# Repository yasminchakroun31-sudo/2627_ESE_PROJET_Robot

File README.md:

# 2627_ESE_PROJET_PAC-Man🤖🗑️
PAC-Man 

### Équipe
- **Yesmine Chakroun** (yasminechakroun31-sudo)
- **Wejdene Hazami**
- **Roua Jaouadi**

### Objectif
Concevoir un robot mobile qui repère, attrape, différencie et dépose des canettes en fonction de leur couleur.

### Timeline
- **Challenge:** 15 janvier 2027
- **Fin semestre:** 16 janvier 2027

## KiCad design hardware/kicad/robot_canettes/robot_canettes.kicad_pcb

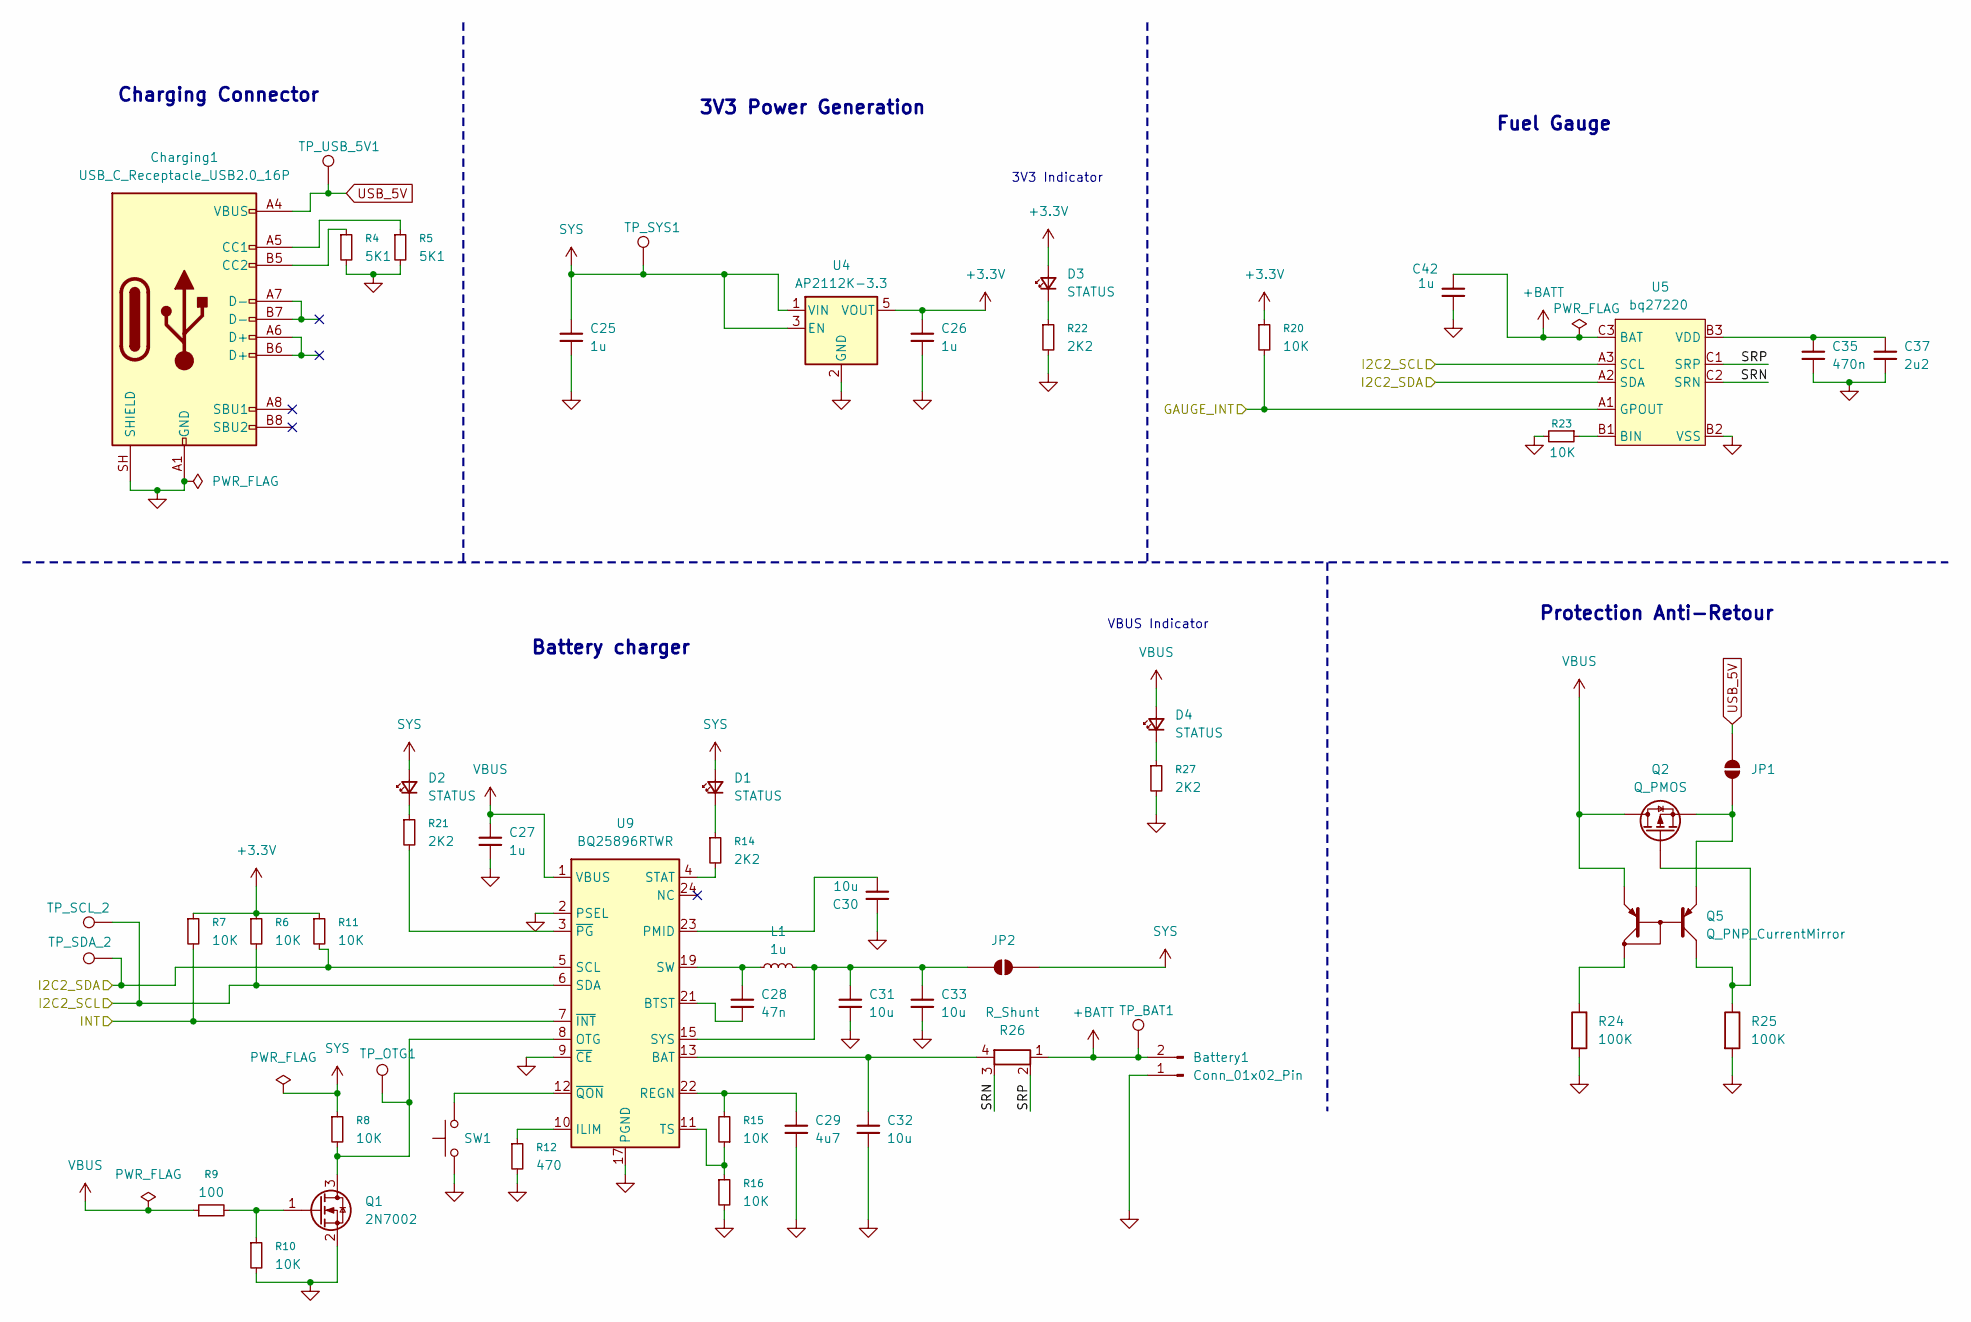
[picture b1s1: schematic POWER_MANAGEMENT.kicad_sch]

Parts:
Battery1: Conn_01x02_Pin; JST_PH_B2B-PH-K_1x02_P2.00mm_Vertical; JLCPCB Part # C131337
C25, C26, C27, C42: 1u; C_0402_1005Metric; JLCPCB Part # C52923
C28: 47n; C_0402_1005Metric; JLCPCB Part # C5254486
C29: 4u7; C_0402_1005Metric; JLCPCB Part # C368809
C30, C31, C32, C33: 10u; C_0603_1608Metric; JLCPCB Part # C19702
C35: 470n; C_0402_1005Metric; JLCPCB Part # C2443202
C37: 2u2; C_0402_1005Metric; JLCPCB Part # C12530
Charging1: USB_C_Receptacle_USB2.0_16P; USB_C_Receptacle_GCT_USB4105-xx-A_16P_TopMnt_Horizontal; JLCPCB Part # C2765186
D1: STATUS; LED_0603_1608Metric; JLCPCB Part # C2287
D2, D3, D4: STATUS; LED_0603_1608Metric; JLCPCB Part # C12624
JP1, JP2: SolderJumper-2_P1.3mm_Open_Pad1.0x1.5mm
L1: 1u; L_APV_ANR4010; JLCPCB Part # C354578
Q1: 2N7002; SOT-23; JLCPCB Part # C8545
Q2: Q_PMOS; SOT-23; JLCPCB Part # C177033
Q5: Q_PNP_CurrentMirror; SOT-363_SC-70-6; JLCPCB Part # C42387345
R4, R5: 5K1; R_0402_1005Metric; JLCPCB Part # C25905
R6, R7, R8, R10, R11, R15, R16, R20, R23: 10K; R_0402_1005Metric; JLCPCB Part # C25744
R9: 100; R_0402_1005Metric; JLCPCB Part # C25076
R12: 470; R_0402_1005Metric; JLCPCB Part # C25117
R14, R21, R22, R27: 2K2; R_0402_1005Metric; JLCPCB Part # C25879
R24, R25: 100K; R_0603_1608Metric; JLCPCB Part # C25803
R26: R_Shunt; R_Shunt_Ohmite_LVK12; JLCPCB Part # C2903499
SW1: SW_SPST_Omron_B3FS-101xP; JLCPCB Part # C271753
TP_BAT1: TestPoint_Pad_D1.5mm
TP_OTG1: TestPoint_Pad_D1.5mm
TP_SCL_2: TestPoint_Pad_D1.5mm
TP_SDA_2: TestPoint_Pad_D1.5mm
TP_SYS1: TestPoint_Pad_D1.5mm
TP_USB_5V1: TestPoint_Pad_D1.5mm
U4: AP2112K-3.3; SOT-23-5; JLCPCB Part # C51118
U5: bq27220; BGA-9_3x3_1.62x1.58mm_Pitch0.5mm; JLCPCB Part # C528617
U9: BQ25896RTWR; Texas_RTW_WQFN-24-1EP_4x4mm_P0.5mm_EP2.7x2.7mm_ThermalVias; JLCPCB Part # C181475

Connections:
+3.3V: C26.1, D3.2 (A), R6.1, R7.1, R11.1, R20.1, U4.5 (VOUT); also elsewhere on the board
+BATT: Battery1.2, C42.2, R26.1, TP_BAT1.1 (1_1), U5.C3 (BAT)
/MCU/GAUGE_INT: R20.2, U5.A1 (GPOUT); also elsewhere on the board
/MCU/I2C2_SCL: R6.2, TP_SCL_2.1 (1_1), U5.A3 (SCL), U9.6 (SDA); also elsewhere on the board
/MCU/I2C2_SDA: R11.2, TP_SDA_2.1 (1_1), U5.A2 (SDA), U9.5 (SCL); also elsewhere on the board
/MCU/INT: R7.2, U9.7 (~INT); also elsewhere on the board
/POWER_MANAGEMENT/SRN: R26.3, U5.C2 (SRN)
/POWER_MANAGEMENT/SRP: R26.2, U5.C1 (SRP)
unnamed: C28.1, L1.1, U9.19 (SW), U9.20 (SW)
unnamed: C32.1, R26.4, U9.13 (BAT), U9.14 (BAT)
unnamed: D1.1 (K), R14.1
unnamed: D2.1 (K), R21.1
unnamed: D3.1 (K), R22.1
unnamed: D4.1 (K), R27.1
unnamed: Charging1.A5 (CC1), R5.1
unnamed: Charging1.B5 (CC2), R4.1
unnamed: JP1.1 (A), Q2.2 (S), Q5.1 (E1)
unnamed: C31.1, C33.1, JP2.2 (B), L1.2, U9.15 (SYS), U9.16 (SYS)
unnamed: Q1.3 (D), R8.2, TP_OTG1.1 (1_1), U9.8 (OTG)
unnamed: Q1.1 (G), R9.2, R10.1
unnamed: Q2.1 (G), Q5.6 (C1), R25.1
unnamed: Q5.3 (C2), R24.1
unnamed: R23.1, U5.B1 (BIN)
unnamed: C35.1, C37.1, U5.B3 (VDD)
unnamed: C28.2, U9.21 (BTST)
unnamed: R12.1, U9.10 (ILIM)
unnamed: C30.2, U9.23 (PMID)
unnamed: C29.1, R15.2, U9.22 (REGN)
unnamed: R14.2, U9.4 (STAT)
unnamed: R15.1, R16.1, U9.11 (TS)
unnamed: R21.2, U9.3 (~PG)
unnamed: SW1.2, U9.12 (~QON)
SYS: C25.1, D1.2 (A), D2.2 (A), JP2.1 (A), R8.1, TP_SYS1.1 (1_1), U4.1 (VIN), U4.3 (EN)
USB_5V: Charging1.A4 (VBUS), Charging1.A9 (VBUS), Charging1.B4 (VBUS), Charging1.B9 (VBUS), JP1.2 (B), TP_USB_5V1.1 (1_1)
VBUS: C27.1, D4.2 (A), Q2.3 (D), Q5.4 (E2), R9.1, U9.1 (VBUS); also elsewhere on the board

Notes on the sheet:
Battery charger
Charging Connector
3V3 Indicator
Fuel Gauge
3V3 Power Generation
Protection Anti-Retour
VBUS Indicator

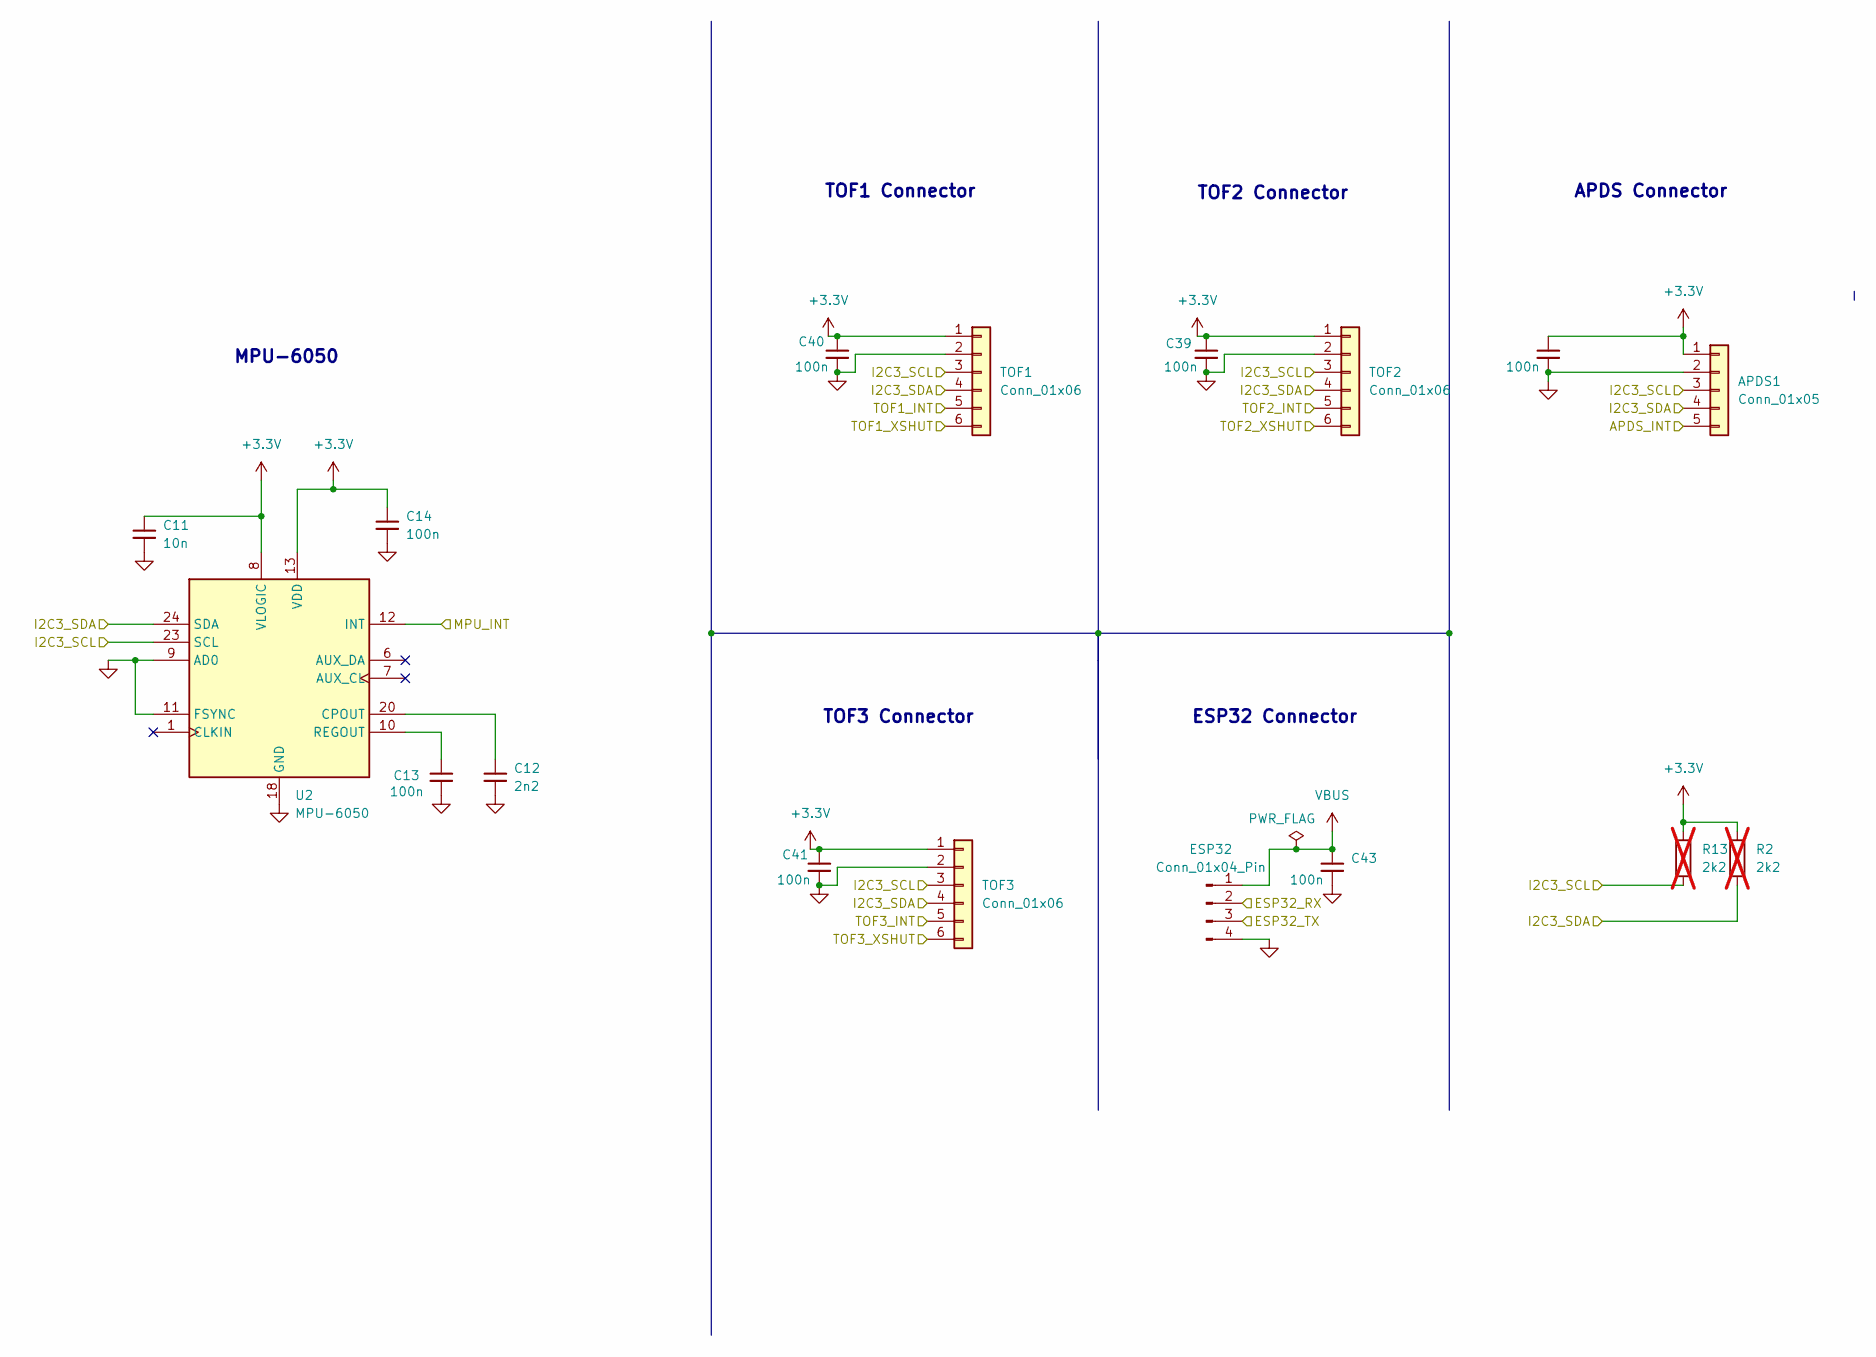
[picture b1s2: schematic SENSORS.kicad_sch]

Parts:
APDS1: Conn_01x05; JST_PH_B5B-PH-K_1x05_P2.00mm_Vertical; JLCPCB Part # C157993
C11: 10n; C_0402_1005Metric; JLCPCB Part # C15195
C12: 2n2; C_0402_1005Metric; JLCPCB Part # C1531
C13, C14, C38, C39, C40, C41, C43: 100n; C_0402_1005Metric; JLCPCB Part # C1525
ESP32: Conn_01x04_Pin; JST_PH_B4B-PH-K_1x04_P2.00mm_Vertical; JLCPCB Part # C131334
R2, R13: 2k2; R_0402_1005Metric; JLCPCB Part # C25879; not fitted
TOF1, TOF2, TOF3: Conn_01x06; JST_PH_B6B-PH-K_1x06_P2.00mm_Vertical; JLCPCB Part # C131342
U2: MPU-6050; InvenSense_QFN-24_4x4mm_P0.5mm; JLCPCB Part # C24112

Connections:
+3.3V: APDS1.1, C11.1, C14.1, C38.1, C39.1, C40.1, C41.1, R2.1, R13.1, TOF1.1, TOF2.1, TOF3.1, U2.8 (VLOGIC), U2.13 (VDD); also elsewhere on the board
/MCU/APDS_INT: APDS1.5; also elsewhere on the board
/MCU/ESP32_RX: ESP32.3; also elsewhere on the board
/MCU/ESP32_TX: ESP32.2; also elsewhere on the board
/MCU/I2C3_SCL: APDS1.3, R13.2, TOF1.3, TOF2.3, TOF3.3, U2.23 (SCL); also elsewhere on the board
/MCU/I2C3_SDA: APDS1.4, R2.2, TOF1.4, TOF2.4, TOF3.4, U2.24 (SDA); also elsewhere on the board
/MCU/MPU_INT: U2.12 (INT); also elsewhere on the board
/MCU/TOF1_INT: TOF1.5; also elsewhere on the board
/MCU/TOF1_XSHUT: TOF1.6; also elsewhere on the board
/MCU/TOF2_INT: TOF2.5; also elsewhere on the board
/MCU/TOF2_XSHUT: TOF2.6; also elsewhere on the board
/MCU/TOF3_INT: TOF3.5; also elsewhere on the board
/MCU/TOF3_XSHUT: TOF3.6; also elsewhere on the board
unnamed: C12.1, U2.20 (CPOUT)
unnamed: C13.1, U2.10 (REGOUT)
VBUS: C43.1, ESP32.1; also elsewhere on the board

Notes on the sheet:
TOF1 Connector
APDS Connector
ESP32 Connector
TOF2 Connector
MPU-6050
TOF3 Connector

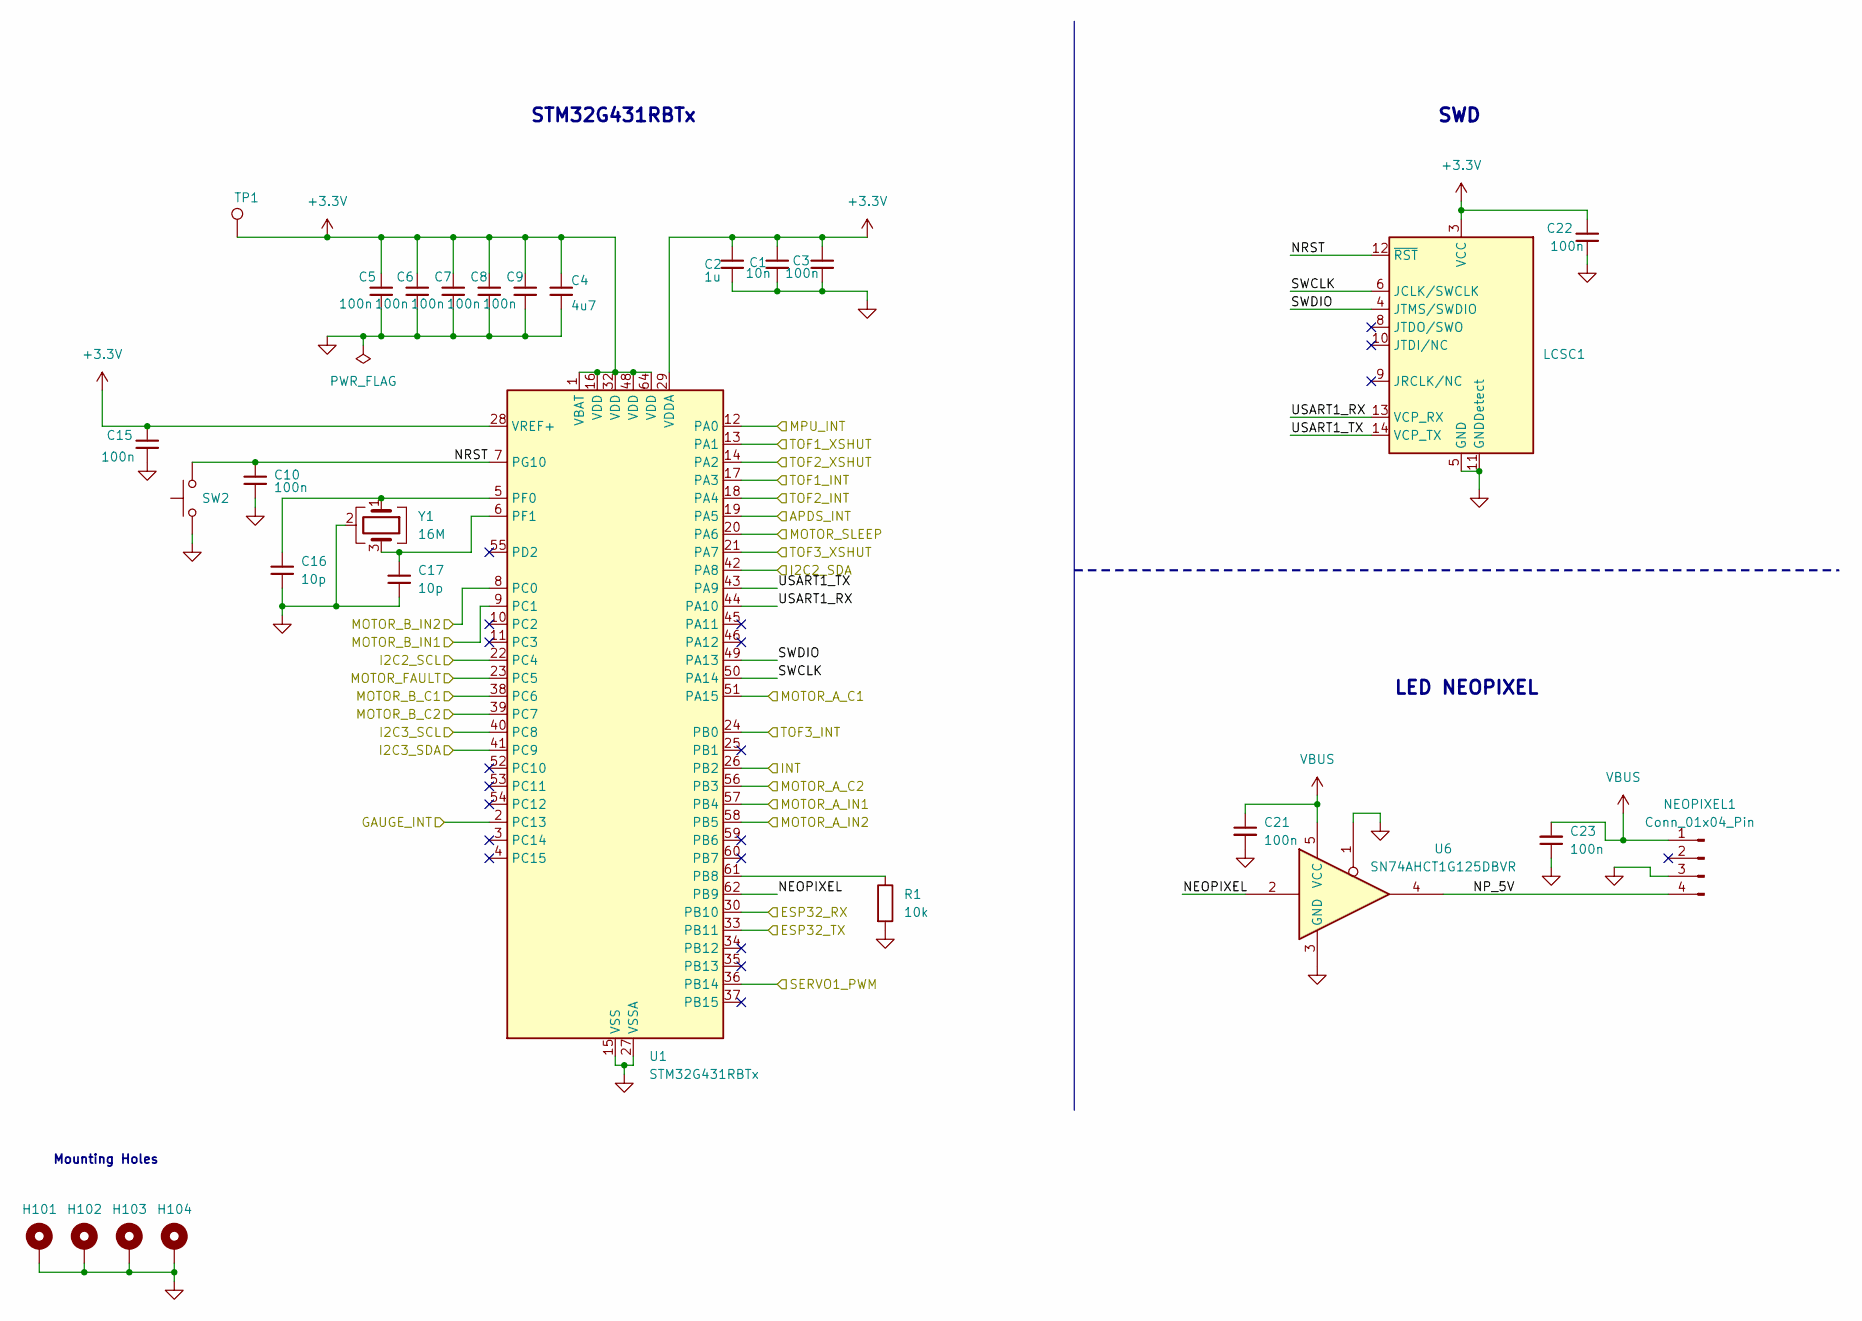
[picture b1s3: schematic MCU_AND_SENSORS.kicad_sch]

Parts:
C1: 10n; C_0402_1005Metric; JLCPCB Part # C15195
C2: 1u; C_0603_1608Metric; JLCPCB Part # C141772
C3, C5, C6, C7, C8, C9, C10, C15, C21, C22, C23: 100n; C_0402_1005Metric; JLCPCB Part # C1525
C4: 4u7; C_0603_1608Metric; JLCPCB Part # C19666
C16, C17: 10p; C_0603_1608Metric; JLCPCB Part # C281766
H101, H102, H103, H104: MountingHole_Pad; MountingHole_3.2mm_M3_Pad_Via
LCSC1: PinHeader_2x07_P1.27mm_Vertical_SMD; JLCPCB Part # C3975190
NEOPIXEL1: Conn_01x04_Pin; JST_PH_B4B-PH-K_1x04_P2.00mm_Vertical; JLCPCB Part # C131334
R1: 10k; R_0402_1005Metric; JLCPCB Part # C25744
SW2: SW_SPST_Omron_B3FS-101xP; JLCPCB Part # C271753
TP1: TestPoint; TestPoint_Pad_D1.5mm
U1: STM32G431RBTx; LQFP-64_10x10mm_P0.5mm; JLCPCB Part # C431633
U6: SN74AHCT1G125DBVR; SOT-23-5; JLCPCB Part # C7484
Y1: 16M; Crystal_SMD_EuroQuartz_MT-4Pin_3.2x2.5mm; JLCPCB Part # C13738

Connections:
+3.3V: C1.1, C2.1, C3.1, C4.1, C5.1, C6.1, C7.1, C8.1, C9.1, C15.1, C22.1, LCSC1.3 (VCC), TP1.1 (1_1), U1.1 (VBAT), U1.16 (VDD), U1.28 (VREF+), U1.29 (VDDA), U1.32 (VDD), U1.48 (VDD), U1.64 (VDD); also elsewhere on the board
/MCU/APDS_INT: U1.19 (PA5); also elsewhere on the board
/MCU/ESP32_RX: U1.30 (PB10); also elsewhere on the board
/MCU/ESP32_TX: U1.33 (PB11); also elsewhere on the board
/MCU/GAUGE_INT: U1.2 (PC13); also elsewhere on the board
/MCU/I2C2_SCL: U1.22 (PC4); also elsewhere on the board
/MCU/I2C2_SDA: U1.42 (PA8); also elsewhere on the board
/MCU/I2C3_SCL: U1.40 (PC8); also elsewhere on the board
/MCU/I2C3_SDA: U1.41 (PC9); also elsewhere on the board
/MCU/INT: U1.26 (PB2); also elsewhere on the board
/MCU/MOTOR_A_C1: U1.51 (PA15); also elsewhere on the board
/MCU/MOTOR_A_C2: U1.56 (PB3); also elsewhere on the board
/MCU/MOTOR_A_IN1: U1.57 (PB4); also elsewhere on the board
/MCU/MOTOR_A_IN2: U1.58 (PB5); also elsewhere on the board
/MCU/MOTOR_B_C1: U1.38 (PC6); also elsewhere on the board
/MCU/MOTOR_B_C2: U1.39 (PC7); also elsewhere on the board
/MCU/MOTOR_B_IN1: U1.9 (PC1); also elsewhere on the board
/MCU/MOTOR_B_IN2: U1.8 (PC0); also elsewhere on the board
/MCU/MOTOR_FAULT: U1.23 (PC5); also elsewhere on the board
/MCU/MOTOR_SLEEP: U1.20 (PA6); also elsewhere on the board
/MCU/MPU_INT: U1.12 (PA0); also elsewhere on the board
/MCU/NEOPIXEL: U1.62 (PB9), U6.2
/MCU/NP_5V: NEOPIXEL1.4, U6.4
/MCU/NRST: C10.1, LCSC1.12 (~RST), SW2.2, U1.7 (PG10)
/MCU/SERVO1_PWM: U1.36 (PB14); also elsewhere on the board
/MCU/SWCLK: LCSC1.6 (JCLK/SWCLK), U1.50 (PA14)
/MCU/SWDIO: LCSC1.4 (JTMS/SWDIO), U1.49 (PA13)
/MCU/TOF1_INT: U1.17 (PA3); also elsewhere on the board
/MCU/TOF1_XSHUT: U1.13 (PA1); also elsewhere on the board
/MCU/TOF2_INT: U1.18 (PA4); also elsewhere on the board
/MCU/TOF2_XSHUT: U1.14 (PA2); also elsewhere on the board
/MCU/TOF3_INT: U1.24 (PB0); also elsewhere on the board
/MCU/TOF3_XSHUT: U1.21 (PA7); also elsewhere on the board
/MCU/USART1_RX: LCSC1.13 (VCP_RX), U1.44 (PA10)
/MCU/USART1_TX: LCSC1.14 (VCP_TX), U1.43 (PA9)
unnamed: R1.1, U1.61 (PB8)
unnamed: C16.1, U1.5 (PF0), Y1.1
unnamed: C17.1, U1.6 (PF1), Y1.3
VBUS: C21.1, C23.2, NEOPIXEL1.1, U6.5 (VCC); also elsewhere on the board

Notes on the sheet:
LED NEOPIXEL
SWD
Mounting Holes
STM32G431RBTx

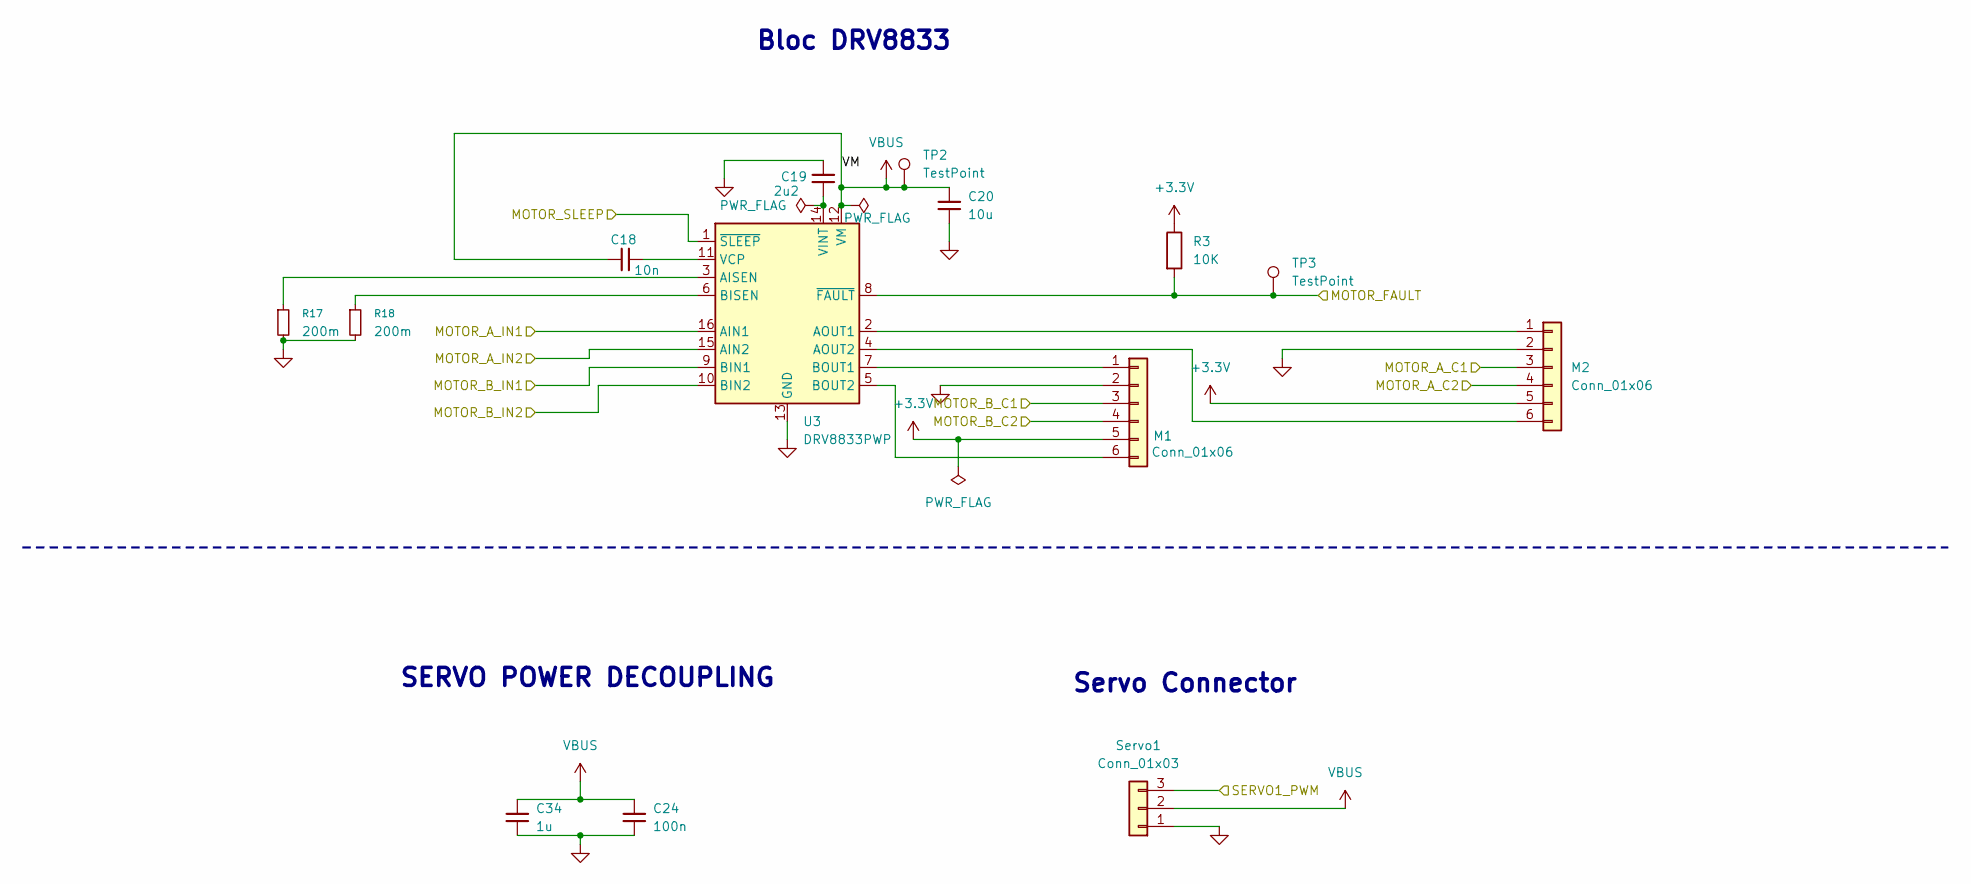
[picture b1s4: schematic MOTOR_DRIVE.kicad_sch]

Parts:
C18: 10n; C_0402_1005Metric; JLCPCB Part # C15195
C19: 2u2; C_0402_1005Metric; JLCPCB Part # C12530
C20: 10u; C_0805_2012Metric; JLCPCB Part # C380332
C24: 100n; C_0402_1005Metric; JLCPCB Part # C1525
C34: 1u; C_0402_1005Metric; JLCPCB Part # C52923
M1, M2: Conn_01x06; JST_PH_B6B-PH-K_1x06_P2.00mm_Vertical; JLCPCB Part # C131342
R3: 10K; R_0402_1005Metric; JLCPCB Part # C25744
R17, R18: 200m; R_1206_3216Metric; JLCPCB Part # C5127778
Servo1: Conn_01x03; JST_PH_B3B-PH-K_1x03_P2.00mm_Vertical; JLCPCB Part # C131339
TP2, TP3: TestPoint; TestPoint_Pad_D1.5mm
U3: DRV8833PWP; HTSSOP-16-1EP_4.4x5mm_P0.65mm_EP3.4x5mm_Mask2.46x2.31mm; JLCPCB Part # C50506

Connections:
+3.3V: M1.5, M2.5, R3.1; also elsewhere on the board
/MCU/MOTOR_A_C1: M2.3; also elsewhere on the board
/MCU/MOTOR_A_C2: M2.4; also elsewhere on the board
/MCU/MOTOR_A_IN1: U3.16 (AIN1); also elsewhere on the board
/MCU/MOTOR_A_IN2: U3.15 (AIN2); also elsewhere on the board
/MCU/MOTOR_B_C1: M1.3; also elsewhere on the board
/MCU/MOTOR_B_C2: M1.4; also elsewhere on the board
/MCU/MOTOR_B_IN1: U3.9 (BIN1); also elsewhere on the board
/MCU/MOTOR_B_IN2: U3.10 (BIN2); also elsewhere on the board
/MCU/MOTOR_FAULT: R3.2, TP3.1 (1_1), U3.8 (~FAULT); also elsewhere on the board
/MCU/MOTOR_SLEEP: U3.1 (~SLEEP); also elsewhere on the board
/MCU/SERVO1_PWM: Servo1.3; also elsewhere on the board
unnamed: M1.1, U3.7 (BOUT1)
unnamed: M1.6, U3.5 (BOUT2)
unnamed: M2.1, U3.2 (AOUT1)
unnamed: M2.6, U3.4 (AOUT2)
unnamed: R17.1, U3.3 (AISEN)
unnamed: R18.1, U3.6 (BISEN)
unnamed: C18.2, U3.11 (VCP)
unnamed: C19.2, U3.14 (VINT)
VBUS: C18.1, C20.1, C24.1, C34.1, Servo1.2, TP2.1 (1_1), U3.12 (VM); also elsewhere on the board

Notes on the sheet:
Servo Connector
SERVO POWER DECOUPLING
Bloc DRV8833

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
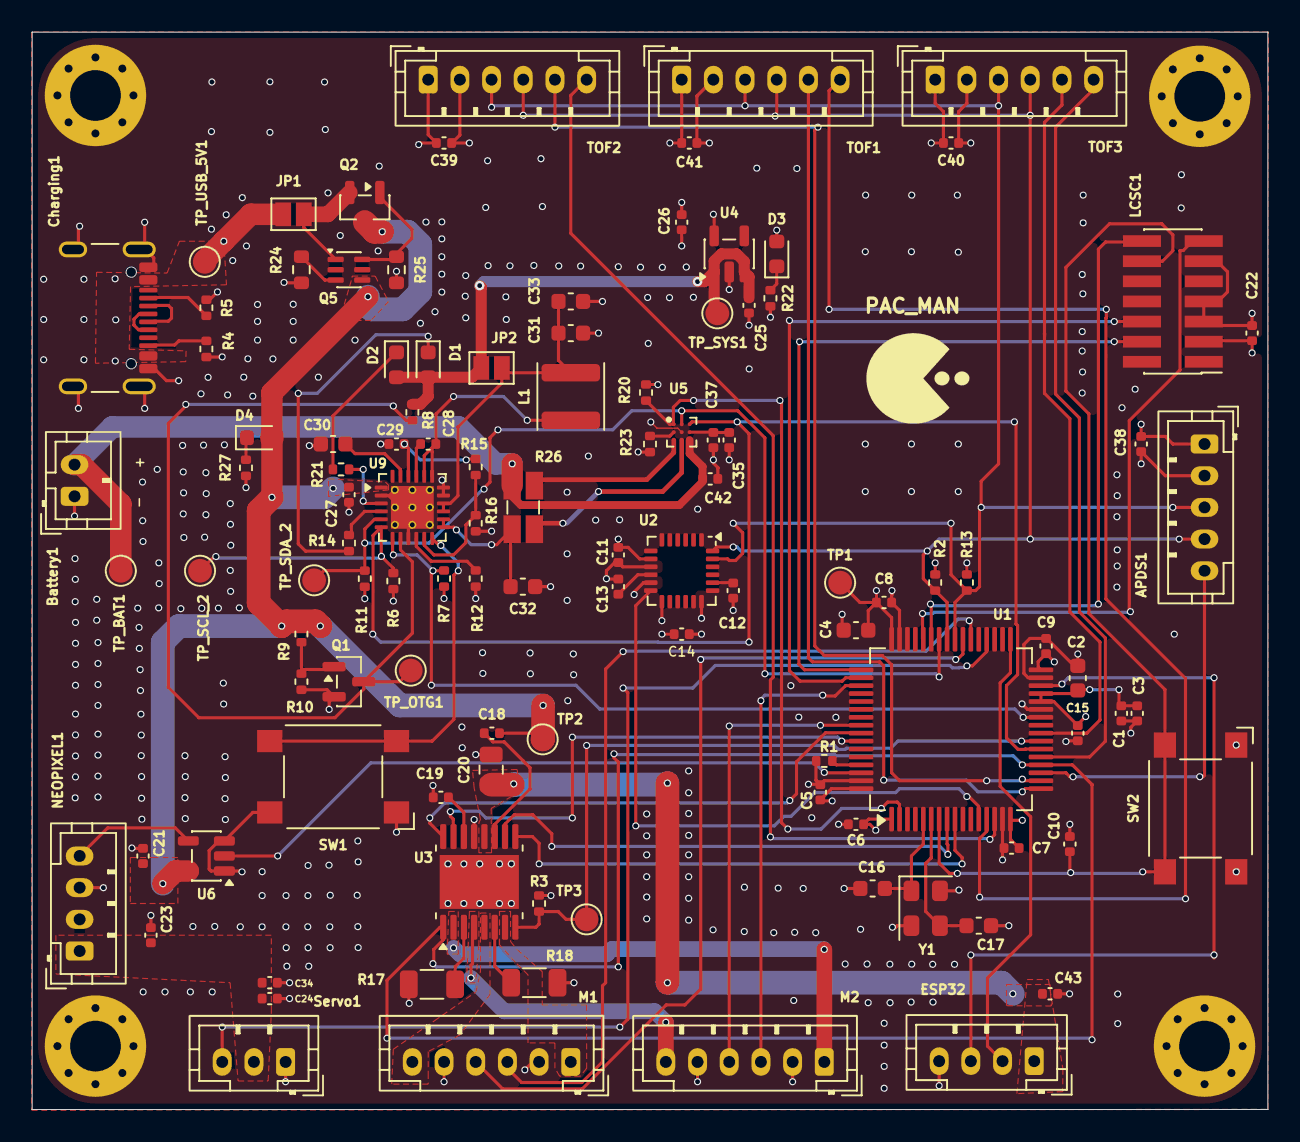
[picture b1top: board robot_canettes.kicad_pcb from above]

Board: 4 copper layers, 78.0 x 68.0 mm, 113 parts (0 on the bottom side), 79 nets.

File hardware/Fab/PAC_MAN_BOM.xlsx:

Comment | Designator | Footprint | JLCPCB Part #
 | LCSC1 | Connector_PinHeader_1.27mm:PinHeader_2x07_P1.27mm_Vertical_SMD | C3975190
 | SW1,SW2 | Button_Switch_SMD:SW_SPST_Omron_B3FS-101xP | C271753
 | TP_BAT1,TP_OTG1,TP_SCL_2,TP_SDA_2,TP_SYS1,TP_USB_5V1 | TestPoint:TestPoint_Pad_D1.5mm
10p | C16,C17 | Capacitor_SMD:C_0603_1608Metric | C281766
2n2 | C12 | Capacitor_SMD:C_0402_1005Metric | C1531
10n | C1,C11,C18 | Capacitor_SMD:C_0402_1005Metric | C15195
47n | C28 | Capacitor_SMD:C_0402_1005Metric | C5254486
100n | C3,C5,C6,C7,C8,C9,C10,C13,C14,C15,C21,C22,C23,C24,C38,C39,C40,C41,C43 | Capacitor_SMD:C_0402_1005Metric | C1525
470n | C35 | Capacitor_SMD:C_0402_1005Metric | C2443202
1u | C2 | Capacitor_SMD:C_0603_1608Metric | C141772
1u | C25,C26,C27,C34,C42 | Capacitor_SMD:C_0402_1005Metric | C52923
1u | L1 | Inductor_SMD:L_APV_ANR4010 | C354578
2u2 | C19,C37 | Capacitor_SMD:C_0402_1005Metric | C12530
4u7 | C4 | Capacitor_SMD:C_0603_1608Metric | C19666
4u7 | C29 | Capacitor_SMD:C_0402_1005Metric | C368809
10u | C20 | Capacitor_SMD:C_0805_2012Metric | C380332
10u | C30,C31,C32,C33 | Capacitor_SMD:C_0603_1608Metric | C19702
200m | R17,R18 | Resistor_SMD:R_1206_3216Metric | C5127778
100 | R9 | Resistor_SMD:R_0402_1005Metric | C25076
470 | R12 | Resistor_SMD:R_0402_1005Metric | C25117
2K2 | R14,R21,R22,R27 | Resistor_SMD:R_0402_1005Metric | C25879
2k2 | R2,R13 | Resistor_SMD:R_0402_1005Metric | C25879
5K1 | R4,R5 | Resistor_SMD:R_0402_1005Metric | C25905
10k | R1 | Resistor_SMD:R_0402_1005Metric | C25744
10K | R3,R6,R7,R8,R10,R11,R15,R16,R20,R23 | Resistor_SMD:R_0402_1005Metric | C25744
100K | R24,R25 | Resistor_SMD:R_0603_1608Metric | C25803
16M | Y1 | Crystal:Crystal_SMD_EuroQuartz_MT-4Pin_3.2x2.5mm | C13738
2N7002 | Q1 | Package_TO_SOT_SMD:SOT-23 | C8545
AP2112K-3.3 | U4 | Package_TO_SOT_SMD:SOT-23-5 | C51118
BQ25896RTWR | U9 | Package_DFN_QFN:Texas_RTW_WQFN-24-1EP_4x4mm_P0.5mm_EP2.7x2.7mm_ThermalVias | C181475
bq27220 | U5 | bq27220:BGA-9_3x3_1.62x1.58mm_Pitch0.5mm | C528617
Conn_01x05 | APDS1 | Connector_JST:JST_PH_B5B-PH-K_1x05_P2.00mm_Vertical | C157993
Conn_01x02_Pin | Battery1 | Connector_JST:JST_PH_B2B-PH-K_1x02_P2.00mm_Vertical | C131337
Conn_01x03 | Servo1 | Connector_JST:JST_PH_B3B-PH-K_1x03_P2.00mm_Vertical | C131339
Conn_01x04_Pin | ESP32,NEOPIXEL1 | Connector_JST:JST_PH_B4B-PH-K_1x04_P2.00mm_Vertical | C131334
Conn_01x06 | M1,M2,TOF1,TOF2,TOF3 | Connector_JST:JST_PH_B6B-PH-K_1x06_P2.00mm_Vertical | C131342
DRV8833PWP | U3 | Package_SO:HTSSOP-16-1EP_4.4x5mm_P0.65mm_EP3.4x5mm_Mask2.46x2.31mm | C50506
MountingHole_Pad | H101,H102,H103,H104 | MountingHole:MountingHole_3.2mm_M3_Pad_Via
MPU-6050 | U2 | Sensor_Motion:InvenSense_QFN-24_4x4mm_P0.5mm
Q_PMOS | Q2 | Package_TO_SOT_SMD:SOT-23 | C177033
Q_PNP_CurrentMirror | Q5 | Package_TO_SOT_SMD:SOT-363_SC-70-6 | C42387345
R_Shunt | R26 | Resistor_SMD:R_Shunt_Ohmite_LVK12 | C2903499
SN74AHCT1G125DBVR | U6 | Package_TO_SOT_SMD:SOT-23-5 | C7484
STATUS | D1 | LED_SMD:LED_0603_1608Metric | C2287
STATUS | D2,D3,D4 | LED_SMD:LED_0603_1608Metric | C12624
STM32G431RBTx | U1 | Package_QFP:LQFP-64_10x10mm_P0.5mm | C431633
TestPoint | TP1,TP2,TP3 | TestPoint:TestPoint_Pad_D1.5mm
USB_C_Receptacle_USB2.0_16P | Charging1 | Connector_USB:USB_C_Receptacle_GCT_USB4105-xx-A_16P_TopMnt_Horizontal | C2765186
